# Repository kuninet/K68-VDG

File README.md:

# SBC6800/6809/6303用 VDGビデオボード

# ★★REV1.1 既知のバグ:  ☆☆
ガーバーデータに誤りがあり、2SC1815と2SC1015のシルク印刷が逆転しています。Q1、Q2の部品番号シルクが正しいです。

## 概要
- SBC68系バスにつながるMC6847 VDG LSIを使用したビデオボードです。
  - REV1基板はアドレスデコードラインにバグがあります。REV2で改善します。プリント基板をお使いの場合は、パターンカット、ジャンパが必要です

## メモリーマップ
- 本基板はVRAMとして8kBのメモリー領域と、VDG設定用レジスタがメモリーマップドI/Oとしてメモリーを占有します。
- 本基板はTomi9さん作のSBC I/O( https://sbc738827564.wordpress.com/2018/08/11/sbc-io-rev02/ )と共存できることを目指しています。

|メモリーアドレス|用途|
|:---|:---|
|$8110|VDG設定用レジスタ|
|\$A000-\$BFFF または \$C000-\$DFFF|ビデオRAM|

## SBC68系バス
- Tomi9さん作のSBC I/O ( https://sbc738827564.wordpress.com/2018/08/11/sbc-io-rev02/ ) に準拠しています。SBC6303ルーズキットとは若干信号線が異なりますのでご注意ください。(ジャンパを実施すれば使えます)

## ディレクトリ構造
|ディレクトリ|用途|
|:---|:---|
|KiCAD/|KiCAD用データ|
|image/|回路図等イメージデータ|

## ライセンス
- MITライセンスで公開します。

## Special Thanks
- 本基板は先人のみなさまの情報で作成することができました。
- pmig96さん・・・MC6847テストサーキット
  - https://pmig96.wordpress.com/2020/07/24/mc6847-test-circuit-part-3/
- Tomi9さん・・・SBC I/Oボード
  - https://sbc738827564.wordpress.com/2018/08/11/sbc-io-rev02/

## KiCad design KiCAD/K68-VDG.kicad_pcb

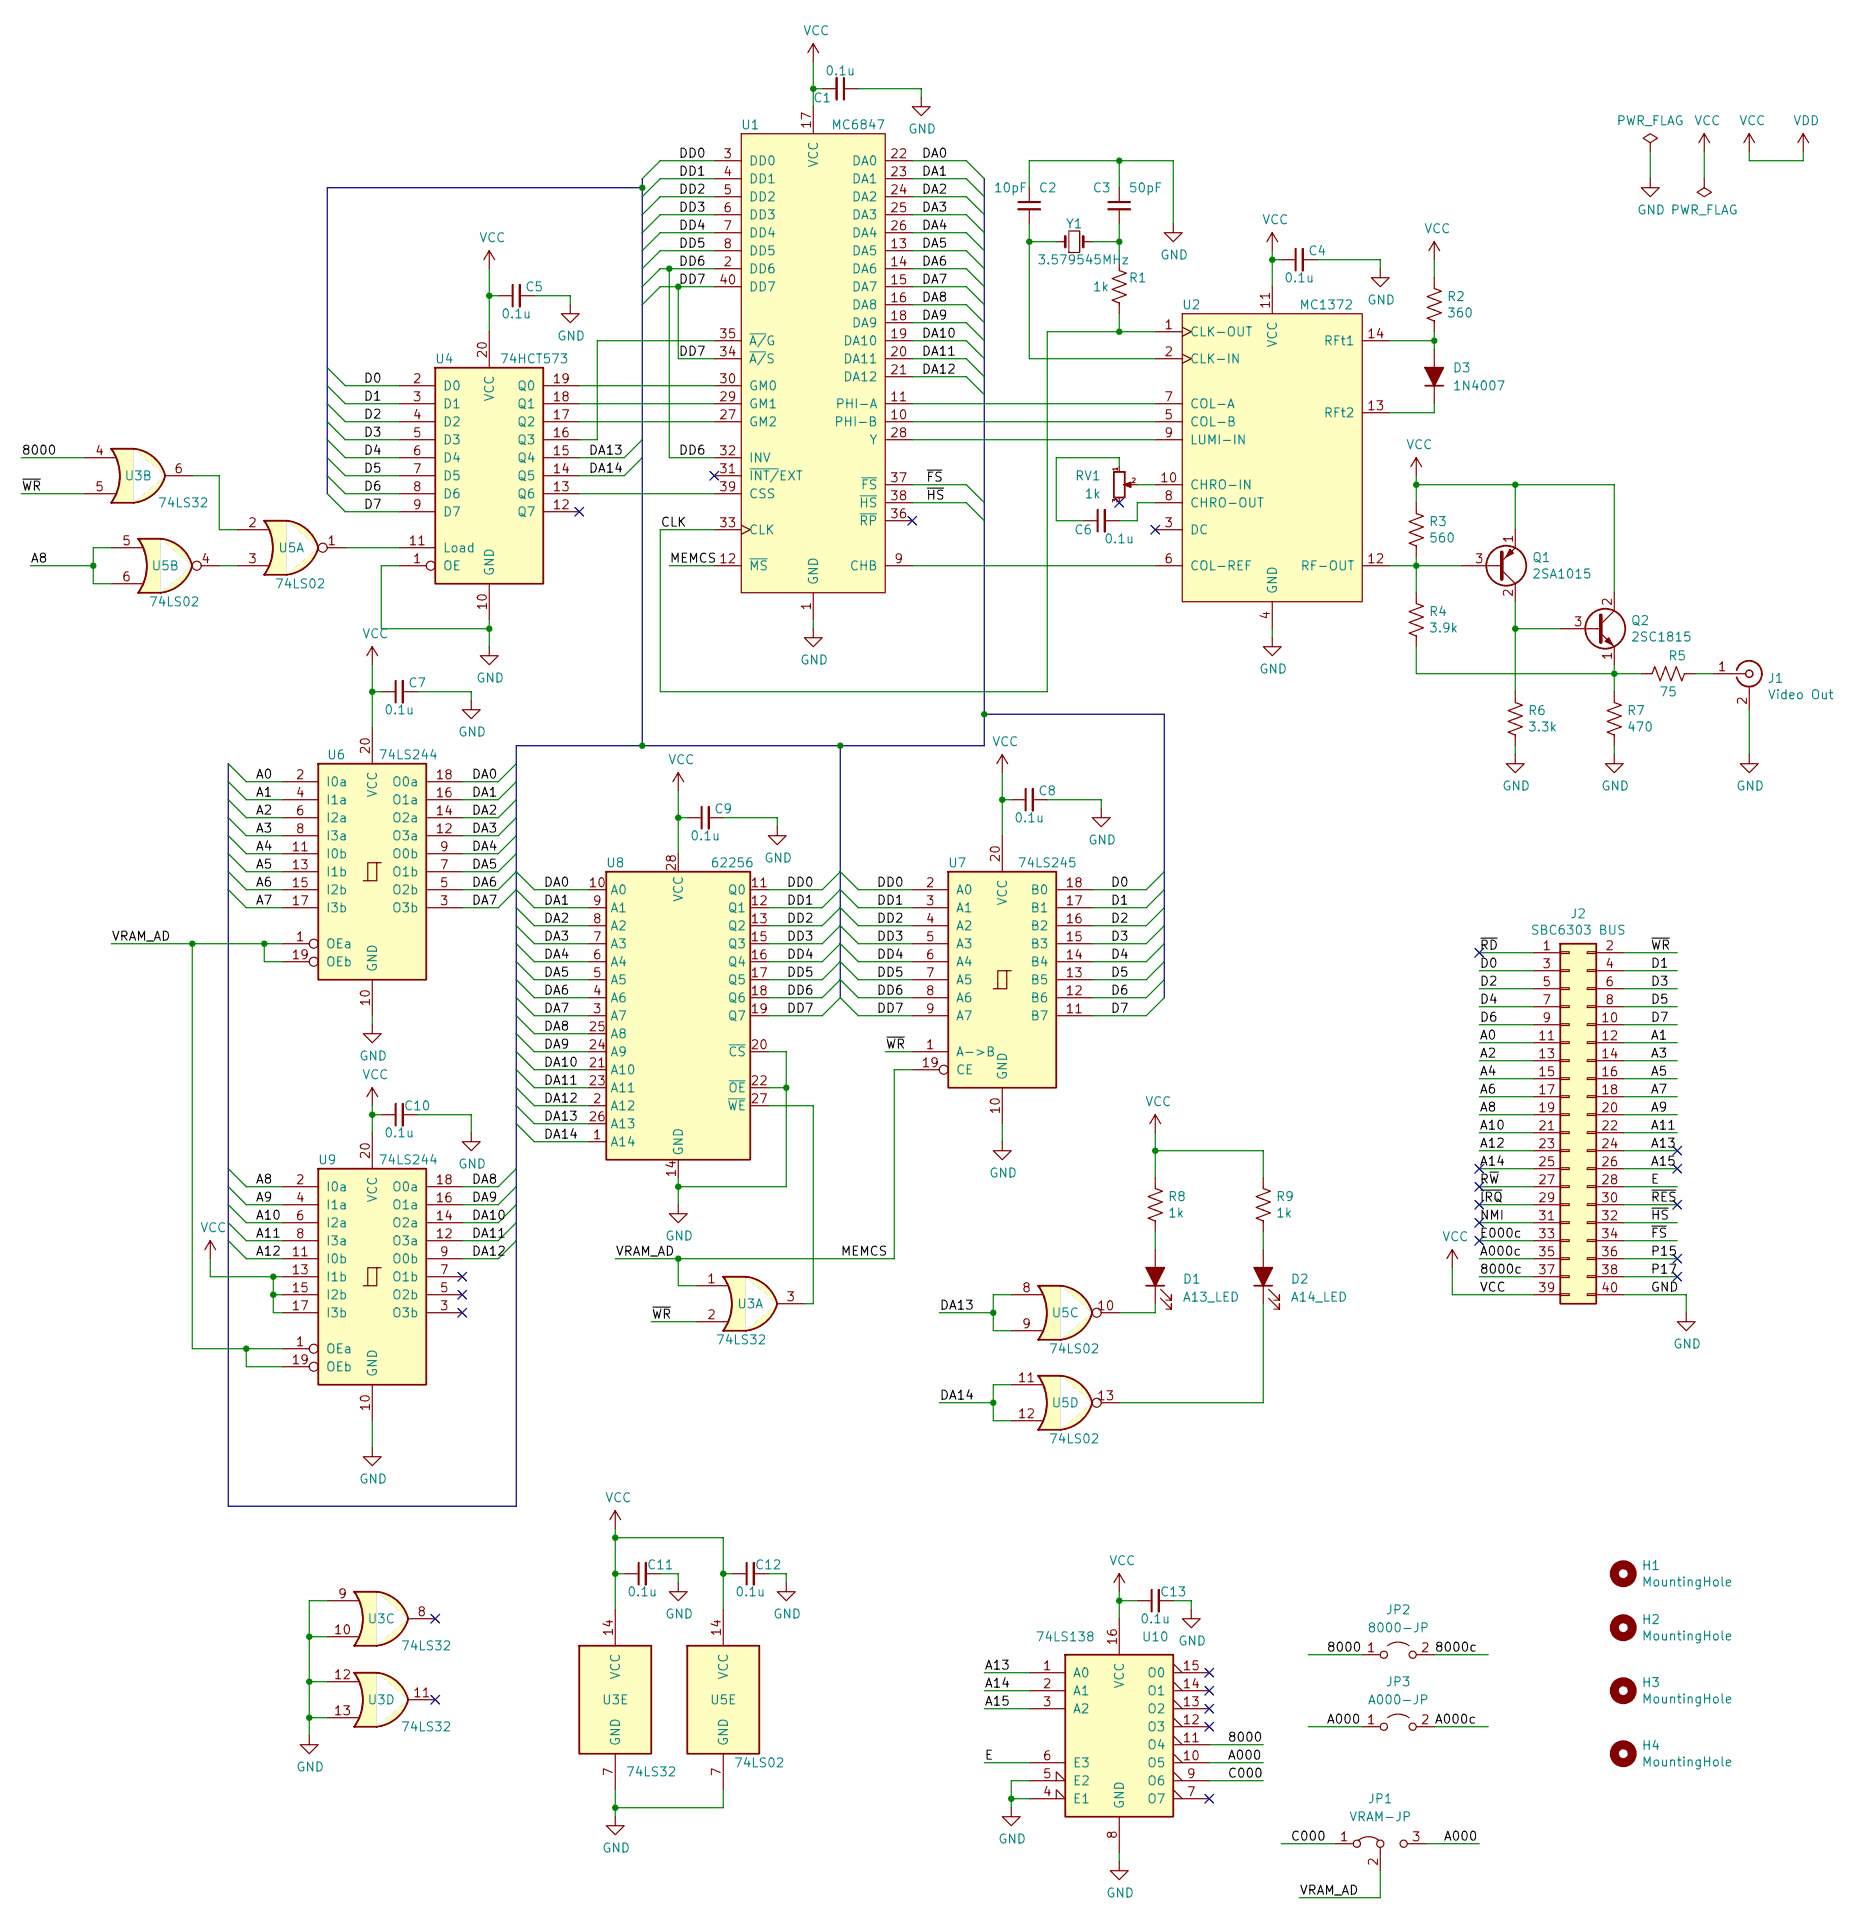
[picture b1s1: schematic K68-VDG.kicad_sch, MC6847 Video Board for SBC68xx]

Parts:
C1, C4, C5, C6, C7, C8, C9, C10, C11, C12, C13: 0.1u; C_Disc_D3.0mm_W1.6mm_P2.50mm
C2: 10pF; C_Disc_D3.0mm_W1.6mm_P2.50mm
C3: 50pF; C_Disc_D3.0mm_W1.6mm_P2.50mm
D1: A13_LED; LED_D3.0mm
D2: A14_LED; LED_D3.0mm
D3: 1N4007; D_DO-34_SOD68_P10.16mm_Horizontal
H1, H2, H3, H4: MountingHole; MountingHole_3.2mm_M3
J1: Video Out; RCAConAE
J2: SBC6303 BUS; PinHeader_2x20_P2.54mm_Horizontal
JP1: VRAM-JP; SolderJumper-3_P1.3mm_Bridged12_RoundedPad1.0x1.5mm
JP2: 8000-JP; SolderJumper-2_P1.3mm_Open_RoundedPad1.0x1.5mm
JP3: A000-JP; SolderJumper-2_P1.3mm_Open_RoundedPad1.0x1.5mm
Q1: 2SA1015; TO-92_Inline_Wide
Q2: 2SC1815; TO-92_Inline_Wide
R1: 1k; R_Axial_DIN0207_L6.3mm_D2.5mm_P5.08mm_Vertical
R2: 360; R_Axial_DIN0207_L6.3mm_D2.5mm_P10.16mm_Horizontal
R3: 560; R_Axial_DIN0207_L6.3mm_D2.5mm_P10.16mm_Horizontal
R4: 3.9k; R_Axial_DIN0207_L6.3mm_D2.5mm_P10.16mm_Horizontal
R5: 75; R_Axial_DIN0207_L6.3mm_D2.5mm_P10.16mm_Horizontal
R6: 3.3k; R_Axial_DIN0207_L6.3mm_D2.5mm_P10.16mm_Horizontal
R7: 470; R_Axial_DIN0207_L6.3mm_D2.5mm_P10.16mm_Horizontal
R8, R9: 1k; R_Axial_DIN0207_L6.3mm_D2.5mm_P10.16mm_Horizontal
RV1: 1k; Potentiometer_Vishay_T73YP_Vertical
U1: MC6847; DIP-40_W15.24mm_Socket_LongPads
U2: MC1372; DIP-14_W7.62mm_Socket_LongPads
U3: 74LS32; DIP-14_W7.62mm_Socket_LongPads
U4: 74HCT573; DIP-20_W7.62mm_Socket_LongPads
U5: 74LS02; DIP-14_W7.62mm_Socket_LongPads
U6, U9: 74LS244; DIP-20_W7.62mm_Socket_LongPads
U7: 74LS245; DIP-20_W7.62mm_Socket_LongPads
U8: 62256; DIP-28_W15.24mm_Socket_LongPads
U10: 74LS138; DIP-16_W7.62mm_Socket_LongPads
Y1: 3.579545MHz; Crystal_HC49-U_Vertical

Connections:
/8000: JP2.1 (A), U3.4, U10.11 (O4)
/8000c: J2.37, JP2.2 (B)
/A0: J2.11, U6.2 (I0a)
/A000: JP1.3 (B), JP3.1 (A), U10.10 (O5)
/A000c: J2.35, JP3.2 (B)
/A1: J2.12, U6.4 (I1a)
/A2: J2.13, U6.6 (I2a)
/A3: J2.14, U6.8 (I3a)
/A4: J2.15, U6.11 (I0b)
/A5: J2.16, U6.13 (I1b)
/A6: J2.17, U6.15 (I2b)
/A7: J2.18, U6.17 (I3b)
/A8: J2.19, U5.5, U5.6, U9.2 (I0a)
/A9: J2.20, U9.4 (I1a)
/A10: J2.21, U9.6 (I2a)
/A11: J2.22, U9.8 (I3a)
/A12: J2.23, U9.11 (I0b)
/A13: J2.24, U10.1 (A0)
/A14: J2.25, U10.2 (A1)
/A15: J2.26, U10.3 (A2)
/C000: JP1.1 (A), U10.9 (O6)
/CLK: R1.2, U1.33 (CLK), U2.1 (CLK-OUT)
/D0: J2.3, U4.2 (D0), U7.18 (B0)
/D1: J2.4, U4.3 (D1), U7.17 (B1)
/D2: J2.5, U4.4 (D2), U7.16 (B2)
/D3: J2.6, U4.5 (D3), U7.15 (B3)
/D4: J2.7, U4.6 (D4), U7.14 (B4)
/D5: J2.8, U4.7 (D5), U7.13 (B5)
/D6: J2.9, U4.8 (D6), U7.12 (B6)
/D7: J2.10, U4.9 (D7), U7.11 (B7)
/DA0: U1.22 (DA0), U6.18 (O0a), U8.10 (A0)
/DA1: U1.23 (DA1), U6.16 (O1a), U8.9 (A1)
/DA2: U1.24 (DA2), U6.14 (O2a), U8.8 (A2)
/DA3: U1.25 (DA3), U6.12 (O3a), U8.7 (A3)
/DA4: U1.26 (DA4), U6.9 (O0b), U8.6 (A4)
/DA5: U1.13 (DA5), U6.7 (O1b), U8.5 (A5)
/DA6: U1.14 (DA6), U6.5 (O2b), U8.4 (A6)
/DA7: U1.15 (DA7), U6.3 (O3b), U8.3 (A7)
/DA8: U1.16 (DA8), U8.25 (A8), U9.18 (O0a)
/DA9: U1.18 (DA9), U8.24 (A9), U9.16 (O1a)
/DA10: U1.19 (DA10), U8.21 (A10), U9.14 (O2a)
/DA11: U1.20 (DA11), U8.23 (A11), U9.12 (O3a)
/DA12: U1.21 (DA12), U8.2 (A12), U9.9 (O0b)
/DA13: U4.15 (Q4), U5.8, U5.9, U8.26 (A13)
/DA14: U4.14 (Q5), U5.11, U5.12, U8.1 (A14)
/DD0: U1.3 (DD0), U7.2 (A0), U8.11 (Q0)
/DD1: U1.4 (DD1), U7.3 (A1), U8.12 (Q1)
/DD2: U1.5 (DD2), U7.4 (A2), U8.13 (Q2)
/DD3: U1.6 (DD3), U7.5 (A3), U8.15 (Q3)
/DD4: U1.7 (DD4), U7.6 (A4), U8.16 (Q4)
/DD5: U1.8 (DD5), U7.7 (A5), U8.17 (Q5)
/DD6: U1.2 (DD6), U1.32 (INV), U7.8 (A6), U8.18 (Q6)
/DD7: U1.34 (~A/S), U1.40 (DD7), U7.9 (A7), U8.19 (Q7)
/E: J2.28, U10.6 (E3)
/E000c: J2.33
/MEMCS: JP1.2 (C), U1.12 (~MS), U3.1, U6.1 (OEa), U6.19 (OEb), U7.19 (CE), U9.1 (OEa), U9.19 (OEb)
/NMI: J2.31
/P15: J2.36
/P17: J2.38
/R~W: J2.27
/~FS: J2.34, U1.37 (~FS)
/~HS: J2.32, U1.38 (~HS)
/~IRQ: J2.29
/~RD: J2.1
/~RES: J2.30
/~WR: J2.2, U3.2, U3.5, U7.1 (A->B)
unnamed: C2.2, U2.2 (CLK-IN), Y1.1
unnamed: C3.2, R1.1, Y1.2
unnamed: C6.1, RV1.1
unnamed: C6.2, U2.8 (CHRO-OUT)
unnamed: J1.1 (In), R5.1
unnamed: Q1.2 (C), Q2.3 (B), R6.1
unnamed: Q1.3 (B), R3.2, R4.1, U2.12 (RF-OUT)
unnamed: Q2.1 (E), R4.2, R5.2, R7.1
unnamed: D3.2 (A), R2.2, U2.14 (RFt1)
unnamed: D1.2 (A), R8.2
unnamed: D2.2 (A), R9.2
unnamed: U1.9 (CHB), U2.6 (COL-REF)
unnamed: U1.10 (PHI-B), U2.5 (COL-B)
unnamed: U1.11 (PHI-A), U2.7 (COL-A)
unnamed: U1.27 (GM2), U4.17 (Q2)
unnamed: U1.28 (Y), U2.9 (LUMI-IN)
unnamed: U1.29 (GM1), U4.18 (Q1)
unnamed: U1.30 (GM0), U4.19 (Q0)
unnamed: U1.35 (~A/G), U4.16 (Q3)
unnamed: U1.39 (CSS), U4.13 (Q6)
unnamed: RV1.2, U2.10 (CHRO-IN)
unnamed: D3.1 (K), U2.13 (RFt2)
unnamed: U3.3, U8.27 (~WE)
unnamed: U3.6, U5.2
unnamed: U4.11 (Load), U5.1
unnamed: U5.3, U5.4
unnamed: D1.1 (K), U5.10
unnamed: D2.1 (K), U5.13

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
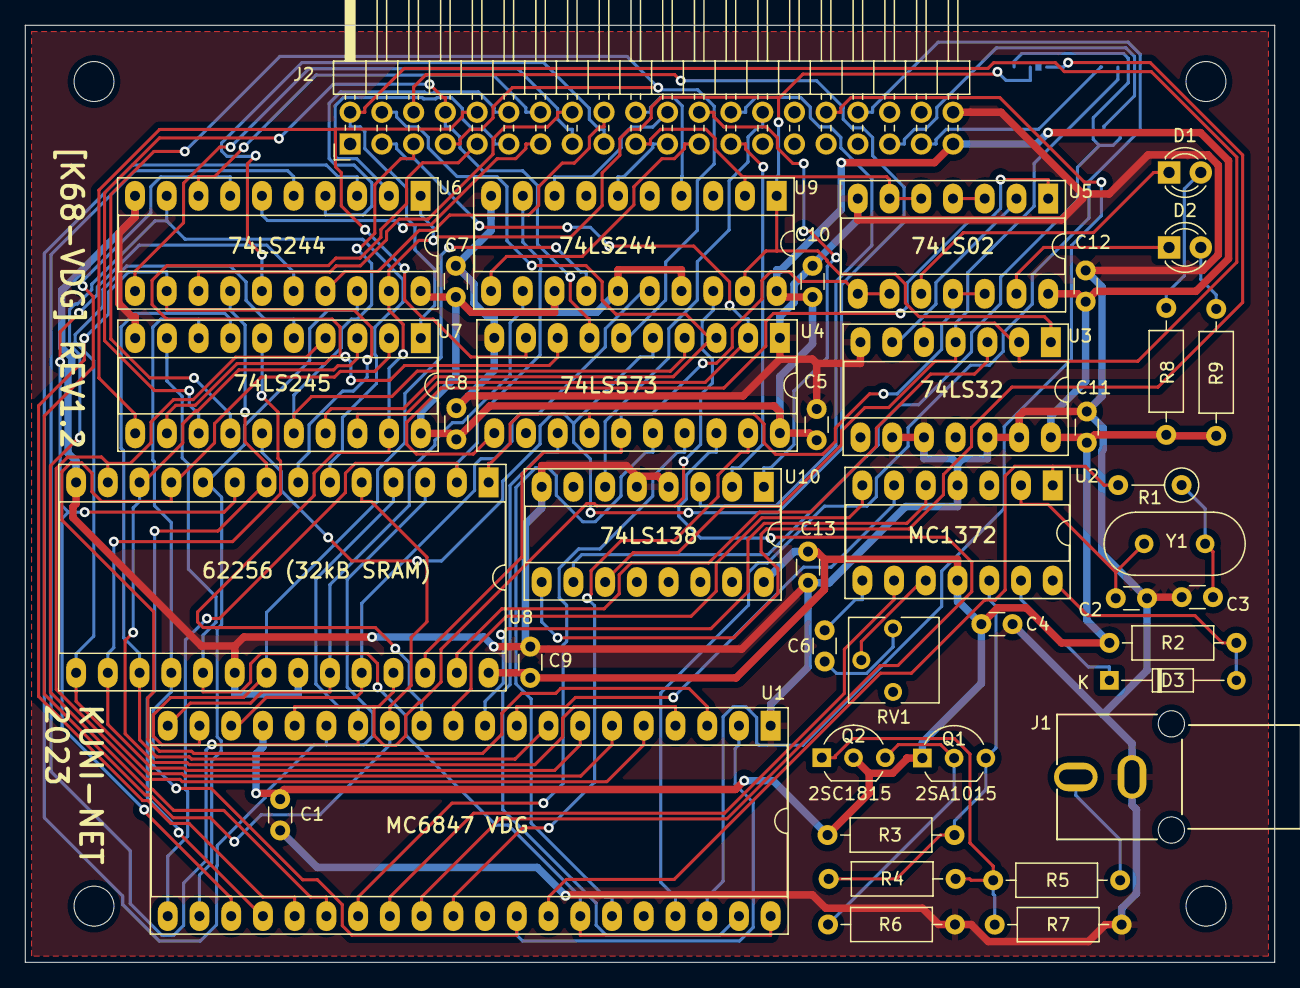
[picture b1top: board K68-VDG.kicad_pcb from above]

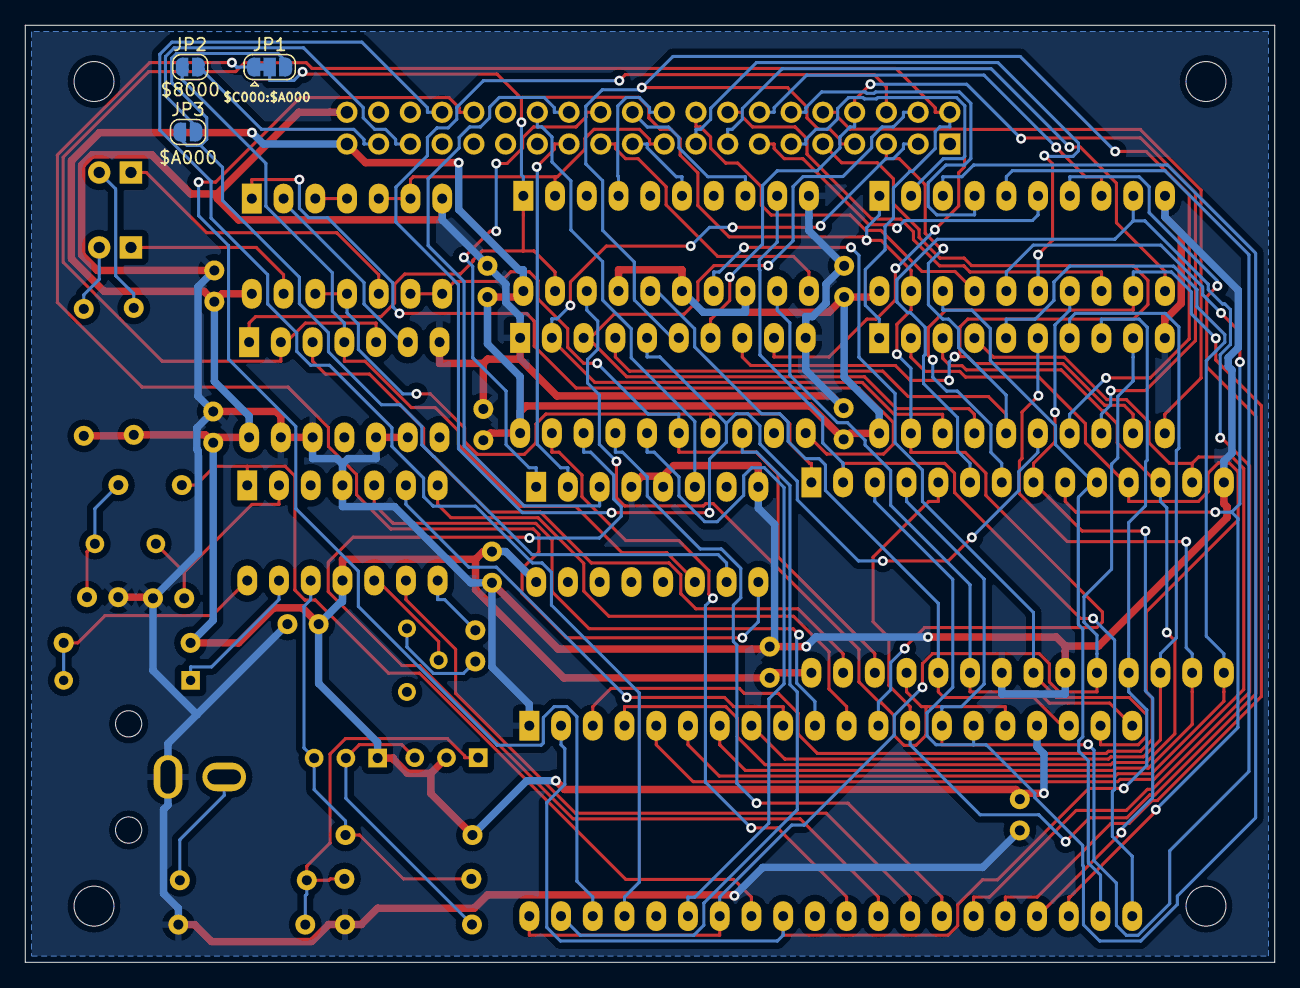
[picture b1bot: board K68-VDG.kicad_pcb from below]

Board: 2 copper layers, 100.0 x 75.0 mm, 48 parts (3 on the bottom side), 88 nets.

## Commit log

2020-09-05 init commit
2020-09-05 Create LICENSE
2020-09-05 回路図等画像追加
2020-09-05 ASCIIキャラクタ一覧表示デモプログラム作成
2020-09-05 ソースコメント追加
2020-09-05 エコーバックテストプログラム追加
2020-09-07 エコーバックプログラム改良
2021-12-18 回路修正、REV1基板ガーバーデータ出力
2021-12-18 回路図イメージ更新
2022-11-04 REV1.1 バグ修正板 ガーバー出力
2023-01-21 基板シルク印刷間違い訂正、回路図C1間違い訂正、v1.2ガーバー出力
2023-01-21 .DS_Storeを削除
2025-03-09 Itty Bitty Computers 2k BASIC用ドライバ更新(未完成)
2025-03-20 echoback サンプル バックスペース対応
2025-03-20 BS処理の場所変更 & VTAM TOP判定
2025-03-20 エコーバックプログラム コメント追加
